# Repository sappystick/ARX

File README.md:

# Arx: PHI-FOLD 233 detector head (design repo)
Everything from the engineering sessions in one place: parametric CAD generators, PCB tooling, simulations, verified results, documents, ready-made prompts and Claude Code / Cowork configuration.

## Quick start (Claude Code or a plain terminal)
```
pip install -r requirements.txt
make setup
make verify-quick        # about 3 minutes: v5 cylinder + base plate + parts + 47 checks + transmit-stage and field simulation
python3 tests/regress.py
```
`make verify-full` (incl. `make audit-system`: wiring audit, stress table, stack-up, voxel interference) adds the receiver simulations, hood, yoke and the display-board routing and Gerbers. Then paste prompts/P00_BOOTSTRAP_CLAUDE_CODE.md into Claude Code.

## What is where
- docs/: DESIGN_STATE (current design), CORRECTIONS (what was wrong), ASSUMPTIONS, OPEN_ITEMS, PROCESS, CONVENTIONS, HISTORY, figures, reference photos.
- prompts/: P00-P10 for Claude Code (the next engineering tasks), prompts/cowork/C00-C06 for Cowork.
- .claude/: slash commands (/status /verify /newpart /route /release), skills, subagents, settings. CLAUDE.md at the root is the project memory.
- src/: generators and simulations (current) + archive/. data/: seeds, legacy boards, results, Gerbers. stl/: curated final STLs with hashes (formers are generated: `make formers-print`).
- scripts/push_to_github.sh: publish to GitHub yourself (plain git; STLs are ordinary binary files, all under GitHub's 100 MB limit).

## Honest scope
Nothing here has been printed, wound, assembled or measured. Performance numbers are modeled from stated assumptions. SB1R-QA/QB, LB1 and CB1D now have KiCad files and Gerbers that pass the repo's own checks and independent DRC; none has been opened in KiCad or a CAM viewer. The rigid-flex spine, CAM/KiCad verification and the DSP are open; the upper assembly (S-stem, trigger, battery dock, twin-cavity shaft) is generated and checked on its meshes but not printed (docs/OPEN_ITEMS.md, docs/design/UPPER_ASSEMBLY_v1.md).

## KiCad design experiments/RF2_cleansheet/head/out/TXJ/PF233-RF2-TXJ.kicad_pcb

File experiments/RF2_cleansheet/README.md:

# RF2 clean-sheet side experiment: transmit formation in a 1-inch head (MODELED)

Question (owner, 2026-10-29): inside the existing diameter and a 1-inch (25.4 mm) height, which layered / stacked / dense transmit-coil formation gives
the most depth together with the best signature data, with the dual-quadrupole receiver (RX-Q) and a central rigid-flex compute bay?
Nothing here touches the baseline. All numbers are MODELED: noise-limited, gold spheres, no ground, no bench data.

`rf2_coil_search.py` (about 20 s) -> `results/rf2_coil_search.json`; `rf2_figure.py` -> `results/rf2_coil_search.png`.

## Method
- Same physics as `src/sim/sim_head1.py`, re-parametrised: RX-Q geometry and noise, sphere step-off response, gate schedule, SNR 3, lateral search grid,
  the turn-off circuit and the first clean gate from the nulled turn-off tail (floor 6 us).
- **Fair comparison:** every candidate gets the baseline's energy per pulse at boost (1/2 x 54 uH x 20 A^2 = 10.8 mJ) and 20 A per switch. With the energy
  fixed, depth depends on the winding geometry through B / sqrt(L) only; the series / parallel split just trades current for inductance, and more switches
  (more total current at the same energy) make the turn-off faster.
- Coil: circular turns (exact elliptic-integral fields and inductances), litz 1.2 mm OD on a dense 1.6 mm grid, window z 3.2-21.9 mm (RX-Q boards below,
  lid + ferrite sheet + clearance above; the display sits in the centre bay), r up to 113.4 mm.
- **Validation:** the built coil through this chain: L 51.5 uH (model 54), 25.0 uT/A at 100 mm (24.56), moment 7.97 A m2 at 20 A (7.96), depth
  0.1 / 1 / 20 g = 90 / 134 / 188 mm (sim_head1: 91 / 136 / 189).

## Results (1 g / 0.1 g gold sphere, RX-Q)
| Formation | 1 g | 0.1 g | Notes |
|---|---|---|---|
| Built coil (25.6 mm tall, does not fit 1 in) | 134 | 90 | first gate 7.1 us |
| 1 in, dense window r 62-113 (spread) ... r 100-113 (rim), 1 switch | 136 | 91-92 | geometry changes depth by <= 1 mm at fixed energy |
| 1 in, rim r 100-113, 2 or 4 switches | 137 | 94 | turn-off 3.8 -> 1.9 us; first gate reaches the 6 us receiver floor |
| + ideal ferrite plane above (UPPER BOUND) | 143 | 98 | the real hood v3 model gave about half of an ideal plane's gain |
| Quadrant set, X mode (horizontal field, shape probe) | 131 | 93 | nearly as deep as the vertical mode with RX-Q |
| Built coil with the figure-8 receiver (sim_head1) | 152 | 99 | the receiver, not the transmit formation, is the largest depth lever |

First-gate sensitivity (4-switch rim coil): 6 / 4 / 3 / 2 us -> 0.05 g 79 / 85 / 88 / 91 mm, 0.1 g 94 / 98 / 100 / 102 mm, 1 g 137 / 139 / 139 / 140 mm.

## Reading
1. **A 1-inch head costs no depth.** At the same pulse energy the dense 1-inch windings match or beat the 25.6 mm stacked coil (136-137 vs 134 mm).
2. **No transmit formation is a big depth lever in this footprint.** Spreading or concentrating the turns, stacking or not: <= 2 mm. Depth moves with
   pulse energy (signal ~ sqrt(E): 2 x energy -> about +7 %), the receiver (figure-8 152 vs RX-Q 136 mm: RX-Q trades about 11 % depth for bearing and
   pinpoint), noise and averaging.
3. **Best formation for depth + signature:** a dense rim winding (r about 100-113 mm, full window height) split into interleaved full-ring branches on
   2-4 switches: fastest turn-off at the same energy (better small / fast targets once the receiver recovers sooner), same depth, frees the centre bay.
4. **Quadrant windings (Z + X / Y modes) give a strong shape channel (X mode 131 mm at 1 g) but a 1 % current mismatch between quadrants puts about
   0.49 V into RX-Q at turn-off** (the built coil's aligned leak is 0.01 mV). The vertical mode must stay on symmetric full-ring branches; X / Y needs
   its own matched pair winding and a receiver that recovers from that leak. Not yet modeled: the pairs' turn-off, X-mode energy, recovery.
5. **Small targets:** the remaining limit is the receiver recovery floor, not the coil: 6 -> 2 us adds about 15 % depth on 0.05 g.

## Not modeled
Ground (mineralisation: the early gates that help small gold also see more ground), coil self-capacitance, litz AC resistance, eddy currents in the head
and the compute bay, the real (finite) ferrite sheet, thermal. Next if pursued: figure-8 / DD / concentric receive options in the same chain with the
rim coil, a matched X / Y pair winding with its turn-off and leak, a finite ferrite sheet, and ground.

## Step 2: receiver architecture, light coil, mass, and an SDC 2300-class comparison (`rf2_receiver_combo.py`, `results/rf2_receiver_combo.{json,png}`)
Owner: targets of 1 g and up only. Same physics and equal energy per pulse (10.8 mJ); every receive channel read with the same preamp noise (1.7 nV/rtHz).

| Architecture (1-inch head, rim transmit coil) | 1 g | 5 g | 20 g | Uniform-ground coupling (rel. CN) |
|---|---|---|---|---|
| QUAD only (built receiver) | 137 | 165 | 190 | 0 by symmetry |
| Figure-8 only (check: sim_head1 at the same noise gives 179 mm at 1 g) | 181 | 223 | 262 | 0 by symmetry |
| Concentric nulled (12 turns r 80-95, 26 bucking turns r 65) | 231 | 284 | 337 | 1.0 |
| **Proposed: rim mono (26 turns, 321 uH, 8.2 A) + QUAD board, mono channel, 15 us gate** | **345** | **439** | **>= 500** | 1.44 |
| same, QUAD channel (bearing, pinpoint, depth ratio) | 131 | 162 | 189 | 0 by symmetry |
| SDC 2300-class 8 in mono at EQUAL electronics, 10 us gate (internals ASSUMED) | 330 | 413 | 494 | 1.40 |

- **Light transmit winding:** 24 turns (16.9 m of litz) give the same depth as the 99-turn dense window (66.6 m): at fixed energy only B / sqrt(L) counts.
- **Depth readout:** the QUAD / mono peak-signal ratio falls monotonically with depth (0.118 / 0.026 / 0.0094 / 0.0043 / 0.0019 at 50 / 100 / 150 / 200 / 300 mm),
  independent of target size for a sphere: depth from the ratio, then size from the amplitude at that depth, type from the decay time constant.
- **Head mass estimate: about 0.53 kg** (component estimates, not weighed; baseline head estimate 2.22 kg). The SDC 2300 is 2.3-2.4 kg as a whole
  detector without batteries; its coil mass is not published, so no head-to-head mass comparison is made.
- **SDC 2300 published facts used:** 8 in round mono, hardwired; Multi Period Fast PI; 2.3-2.4 kg without batteries; 4 x C cells, about 7 h; no
  discrimination, depth readout or pinpoint mode; LED indicator + audio; waterproof 3 m. Not published: turns, inductance, current, timing, noise, depth.
  The SDC row is therefore an 8 in mono with OUR electronics, not the real detector.
- **Reading:** the mono channel is the deepest receive option for >= 1 g (the full transmit coil is the receiver: the largest area); the proposed
  head's mono is about 4-5 % deeper than an 8 in mono at equal electronics, from the larger diameter only. What the proposed head adds is the QUAD
  channel (bearing, peak-null-peak pinpoint, a ground-symmetric second channel) and the ratio depth readout.
- **The bucking-turn cap:** an unconstrained concentric search chose 1239 turns at r 12 mm (cannot be laid out; capacitance and resistance noise not
  modeled); the search caps the bucking winding at 30 board-trace turns (0.3 mm pitch, 4 layers, a 6 mm band holds about 80).
- **Not modeled, and decisive in the field:** real ground. The mono and CN channels see a uniform viscous ground strongly and need ground balance
  (as the SDC has); the QUAD and figure-8 cancel uniform ground only while the head stays level and at constant height. Hot rocks, layering and
  sweep tilt are not modeled. Also not modeled: the mono's damping-resistor noise and preamp overload recovery (the 1.7 nV/rtHz is generous to both
  monos), self-capacitance, eddy currents in the compute bay.

## Step 3: mineralised ground and how to cancel it (`rf2_ground.py`, `results/rf2_ground.{json,png}`)
Ground model (Born approximation, uniform magnetically viscous half-space, ASSUMED parameters swept): emf = I chi_v / mu0 x G(h, tilt) x [t^-a - (t+T)^-a];
G = integral of Bt . Br over the ground. Varies while sweeping: height 15-45 mm, tilt about 3 deg, exponent a = 1 +- 0.03, patchy amplitude x lognormal(0, 0.3).
chi_v 2e-6 / 2e-5 / 2e-4 (mild / moderate / severe) is an ASSUMED order of magnitude, not a measured soil. Optimal linear detectors (SINR = s' R^-1 s).

| 1 g depth (mm) | none | mild | moderate | severe |
|---|---|---|---|---|
| D1 mono, no ground balance | 362 | 0 | 0 | 0 |
| D2 mono, time-domain balance | 366 | 244 | 221 | 204 |
| **D3 mono, multi-period (PWM flat-top) balance** | 367 | **249** | **228** | **221** |
| D4 quadrupole pair only, no balance | 137 | 128 | 88 | 0 |
| D5 / D6 mono + QA + QB space-time (with / without multi-period) | = D2 / D3 | | | |
| D7 + dual transmit (inner coil, alternate pulses) | 350 | 239 | 220 | 212 |
| SDC 2300-class 8 in mono, multi-period (equal electronics) | 342 | 235 | 216 | 209 |

- The quadrupole sees uniform ground only through tilt, at second order (level ground: 1e-29 vs the mono's 4e-11; 3 deg tilt about 1e-3 of the mono).
- In uniform ground the time signature does the work: multi-period (two PWM on-times) is the best method; the quadrupole array and dual transmit add nothing
  (dual transmit splits the pulses and loses a little).
- What costs depth is the spread of the ground's decay exponent: tracking it (severe ground, 1 g) 0.03 -> 0.01 -> 0.003 -> 0: 221 -> 227 -> 249 -> 274 mm.
  Even a perfectly known exponent leaves about 25 % loss against no ground: the unknown 1/t amplitude overlaps the target's decay.

## Step 4: a firmware-style ground-tracking detector on simulated sweeps (`rf2_ground_dsp.py`, `results/rf2_ground_dsp.json`)
Frames of 36 numbers (mono at both PWM periods, QA / QB with both periods averaged: every pulse is received by every coil); ground learned as a low-rank
subspace per receiver (eigen-directions above the electronic noise, EWMA, an 80-frame "ground pump" at switch-on, a guard window so a target's flanks are
not learned, an anti-lock rule); GLRT over a bank of 12 decay constants, silent below the chi-square threshold (false-alarm rate 1e-5 per frame).
- **0 false-alarm frames** on target-free sweeps over severe and moderate ground.
- 1 g detected at 100, 150, 200 mm (severe and moderate); decay constant 27.3 us against 27.9 us true -> "small gold". 5 g at 250-280 mm and 20 g at
  300 mm were NOT detected in one pass (peak statistic 20-24 vs threshold 25.9): the adaptive detector with a strict false-alarm rate reaches less than
  the oracle study above.
- Readouts, honestly: the quadrupole's single-pass range for 1 g is about 80-100 mm (noise-only check: SNR 29 / 4 / 0.5 at 60 / 100 / 150 mm), so bearing
  and ratio depth only work close in; the mono response width resolves depth only beyond about 160 mm (the 230 mm coil sets a floor); between, depth
  is "<= 160 mm" and size an upper bound. Next: a trigger-held pinpoint (boost + averaging) for bearing / depth / size, and the 100-160 mm gap.
- Mistakes found and fixed on the way: rank 3 ground subspace (the ground needs about 7 directions: 79 of 81 frames falsely triggered); a quadrupole
  "signal" that was the best of 81 noise frames (gate raised to SNR 5); a tracker that learned the target's flanks (guard window); quadrupole fed only
  half the pulses.

## Step 5: is every coil fully off when the receivers listen? (`rf2_timing.py`, `results/rf2_timing.json`)
Two coupled coils with node capacitance, damping, clamp diode / capacitor and the switch's body diode; nonlinear part by ODE, linear tail exact (matrix
exponential, resolved to 100 nV); preamp recovery 2 us and coil capacitance 500 pF ASSUMED.

| Case (first clean gate, us) | mono | QUAD | current induced in idle coil B |
|---|---|---|---|
| rim coil alone, critical damping | **16.3** | 9.2 | - |
| rim coil alone, baseline damping ratio (underdamped) | 24.8 | 13.5 | - |
| + idle B wound the same sense | 21.7 | 11.6 | 0.34 A (through its damping only) |
| + idle B wound the opposite sense | **36.7** | 24.0 | **1.5 A** (its switch's body diode conducts) |
| + idle B, clamp not yet charged (first pulses) | 27.2 | 17.1 | 1.6 A |

- The assumed 15 us mono gate holds for a critically damped mono (16.3 us): 1 g depth 363 vs 367 mm, severe ground 221 either way. Use critical damping.
- Dual transmit needs: both coils wound the same sense, clamps pre-charged before the first pulse, and about 5 us more delay from the idle coil's damping.
- Nothing is left at the 2.5 ms period (residual about 0).

## Step 6: trigger-held pinpoint (`rf2_pinpoint.py`, `results/rf2_pinpoint.json`)
After a detection: hold the trigger and make one slow pass back over the spot (+-250 mm), BOOST 2.5 x energy per pulse (about 13 A, inside the 20 A switch
rating, a few seconds) and k = 4 or 16 x more pulses per 10 mm frame. Same tracker and detector as step 4.
- **Bearing works close in:** 1 g at 100 mm: quadrupole SNR 5-9 (scan pass 2.6-2.9), bearing axis within about 1-11 deg of the truth (e.g. 166.9 vs 167.5,
  168.1 vs 168.7, 139.8 vs 128.7); depth from the quadrupole / mono ratio 80-88 mm (biased low, true 100); size 0.6-0.8 g (true 1 g).
- **It does not close the 100-160 mm gap:** from 130 mm the quadrupole stays at SNR 2-4 even 16 x slower with boost, while the mono statistic grows
  10-30 x. The quadrupole there is limited by ground reaching it through head tilt and by its own steep fall-off, not by noise; averaging cannot fix it.
- **Lift test (second pass 50 mm higher; ratio of the two mono peaks, size-independent): NOT working yet.** With the scan height wobble (sd 8 mm) the
  ratio is dominated by the unknown height (about 25 % per 8 mm at 150 mm range); with the height known exactly the errors are still 20-50 % (1 g at
  130 mm -> 108, 5 g at 200 mm -> 276). Fixed on the way: both passes must be fitted at the same decay constant. Unresolved error sources (tilt per frame,
  10 mm sampling, the tracker re-learning between passes) are open. A deep depth readout needs a known height (ground-referenced height from the
  ground signal itself, a height sensor, or a rest-on-the-ground pinpoint with a fixed lift spacer) and this error budget resolved.

## Step 7: golden-angle petals in a thin ring around the rim (owner idea; `rf2_petal_ring.py`, `results/rf2_petal_ring.json`)
Same chain and equal energy per pulse; the petal set is transmitter and receiver (mono style); first gate 16.3 us; noise-limited, no ground.
| Formation (1 / 5 / 20 g, mm) | 1 g | 5 g | 20 g | net moment, A m2 |
|---|---|---|---|---|
| Reference: rim mono, 26 turns | 342 | 437 | >= 500 | 8.23 vertical |
| Best petal ring: 8 flat petals, radius 40 mm, 1 layer | 242 | 312 | 379 | 4.90 vertical |
| 6 flat petals r 25 mm / 13 flat petals r 15 mm | 132 / 84 | 185 / 121 | 237 / 165 | 1.92 / 1.38 |
| Best standing (radial) petals: 8 x r 40 mm, 6 layers | 187 | 230 | 267 | about 0.1 horizontal |
| Tangential petals | 0-118 | 0-136 | 0-151 | about 0.1 horizontal |
Reading: depth follows the magnetic moment (turns x current x enclosed area) the coil can make with the pulse energy. One loop around the full rim
encloses the most area; splitting the same wire into small petals encloses far less (moment 4.9 vs 8.2 A m2 at best), and standing petals point their
moments in different directions around the ring, which nearly cancel (net about 0.1 A m2): their field falls off faster and the depth drops. The golden
angle changes the near-field pattern, not the far field that reaches depth. Layering petals vertically does not recover it.

## Step 8: separate jobs: rim coil transmits, a disc coil in the centre receives (owner idea; `rf2_disk_rx.py`, `results/rf2_disk_rx.json`)
Unnulled receive coil on the base board (2 oz traces, 150 pF and 2 us preamp recovery ASSUMED, critically damped); first gates from the coupled turn-off;
noise includes the coil resistance and its damping resistor; the rim coil's own mono channel is kept as a second channel (SNR combined in quadrature).
| Receive pattern, turns | first gate, us | 1 g: disc / mono / both | 5 g: disc / mono / both | flyback on the receive coil |
|---|---|---|---|---|
| inner r 15-60, 48 | 16.7 | 272 / 340 / 343 | 346 / 436 / 439 | 67 V |
| disc r 15-100, 48 | 20.2 | 310 / 336 / 348 | 398 / 434 / 447 | 199 V |
| sunflower (equal area per turn) r 15-100, 48 | 21.8 | 323 / 334 / 351 | 416 / 433 / 453 | 265 V |
| **outer ring r 85-100, 48** | 26.7 | **344 / 327 / 359** | **448 / 429 / 467** | **484 V** |
- The best separate receiver matches the rim coil as its own receiver (344 vs 327-341 mm at 1 g); both channels together add about 5 % (359 mm).
- Why not more: the rim coil as a receiver already encloses the largest area possible in this footprint; a disc inside it encloses less, and more
  turns raise its signal but slow its recovery (gate 16.7 -> 26.7 us) and its coupling to the transmitter (k up to 0.51).
- Ground pickup is the same order as the mono (0.8-0.97 of it): the disc receiver needs ground balance too.
- High voltage: unnulled, the receive coil sees up to 484 V at turn-off, so its board falls under rule 6 (>= 1.0 mm clearance, 630 V input
  protection) unless a bucking winding nulls it (step 2: the nulled concentric receiver reached 231 mm).

## Step 9: external interference and cancelling it (`rf2_emi.py`, `results/rf2_emi.json`)
Interference amplitudes and spectra ASSUMED (swept), uniform over the head; 1 g depth, mono / quadrupole (0.1 % lobe imbalance ASSUMED), mm.
| Source | matched, fixed rate | matched, jittered | learned, fixed | learned, jittered | learned + jitter + 3-axis REF on the shaft |
|---|---|---|---|---|---|
| none | 360 / 138 | 360 / 138 | 364 / 139 | 364 / 139 | 360 / 139 |
| power line, rural 0.05 uT | 164 | 193 | 273 | 288 | **349** |
| power line, under a line 1 uT | 51 | 74 | 222 | 230 | **295** |
| VLF 1 nT at exactly 20.000 kHz (in step with 400 Hz) | 130 | 225 | 354 | 354 | 360 |
| VLF 10 nT at 19.8 kHz | 360 | 130 | 364 | 353 | 359 |
| electric fence 50 nT at 20 m (1 pulse/s) | 173 | 176 | 327 | 205 | **360** (fence pulses blanked) |
The quadrupole stays at 138-139 mm in every case: it rejects uniform interference by symmetry (net area 0; the imbalance leaks about 1e-5 of the mono).
- **Learning the interference** (listen-only frames, whitening) is the largest single step: steady interference makes a fixed pattern across the gates
  that the detector can cancel. **Jitter is not always better**: it helps a simple matched detector against an in-step tone (130 -> 225), but it
  turns a learnable pattern into noise for the learning detector, and for a tone near (not at) a pulse-rate multiple the fixed rate already cancels it
  (19.8 kHz: fixed 360, jittered 130). The firmware should choose the rate per site (like an automatic frequency offset), not jitter blindly.
- **The 3-axis reference coil** (0.6 m up the shaft, adaptive weights) recovers most of the power-line loss (230 -> 295 under a line; 288 -> 349 rural)
  and, with blanking, all of the fence loss; its own noise costs about 1 % depth. Residual: the field difference between the shaft and the head (3 %
  for a line source at 20 m). Fence results vary from run to run (few hits per run).
- **Split-ring (MWO-style) shield**: a split 3 mm trace's own eddy decay is about 0.8 us (1 mm trace 0.26 us), down by e^-21 at the 16.3 us first gate;
  the same trace closed into a ring decays with 6 us, inside the receive window. Split rings are eddy-safe as an electrostatic shield; closed rings are not.
  (An earlier statement in the session that the split trace decays in about a nanosecond was wrong by a factor of 1000; corrected here.)

## Step 10: head v1 layout, seats, shield board, wiring, power and timing (`head/`, `HANDOFF_RF2.md`)
The design implementation set: `head/rf2_head.py` (spec + every printed part, seat and envelope), `head/rf2_shield_pcb.py` (SH1: KiCad DRC 0 / 0, Gerbers +
drill, loop-free), `head/rf2_head_check.py` (measured checks, all pass; mass about 702 g), `head/rf2_wiring.py` (C01-C12, ADC map, power, timing; slot
probes), figures `head/out/rf2_head_layout.png` and `head/out/rf2_wiring.png`. Every part, function and open step: `HANDOFF_RF2.md`.

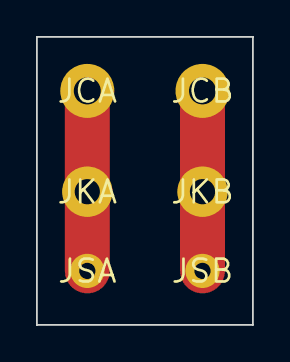
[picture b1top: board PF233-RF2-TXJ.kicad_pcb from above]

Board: 2 copper layers, 12.0 x 16.0 mm, 6 parts (0 on the bottom side), 2 nets.

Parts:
JCA: coil A; WIRE_LITZ
JCB: coil B; WIRE_LITZ
JKA: cable A; WIRE_AWG18
JKB: cable B; WIRE_AWG18
JSA: sense A; WIRE_SENSE
JSB: sense B; WIRE_SENSE

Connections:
TX_A: JCA.1, JKA.1, JSA.1
TX_B: JCB.1, JKB.1, JSB.1

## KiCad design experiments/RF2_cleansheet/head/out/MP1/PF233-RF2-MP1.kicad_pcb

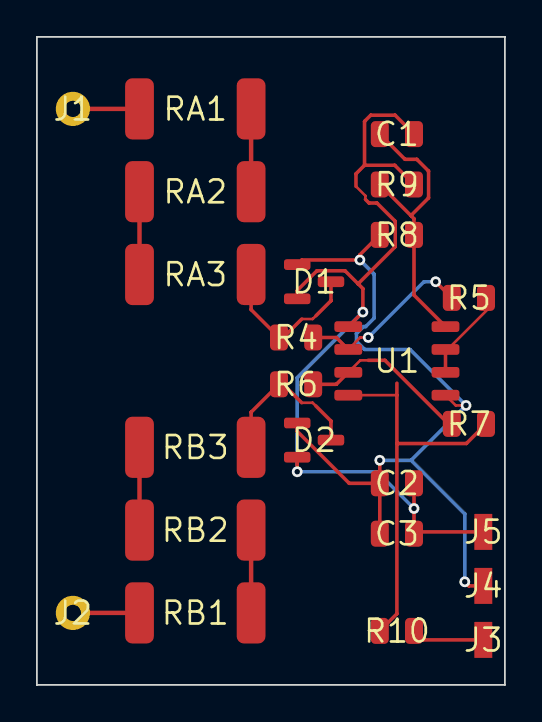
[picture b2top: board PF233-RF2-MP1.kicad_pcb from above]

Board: 2 copper layers, 26.0 x 36.0 mm, 24 parts (0 on the bottom side), 16 nets.

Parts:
C1, C3: 100n; C0805
C2: 10u; C0805
D1, D2: BAV199
J1: COIL_A; WIRE_SENSE
J2: COIL_B; WIRE_SENSE
J3: MONO_OUT; FLEX_PAD
J4: +5VA; FLEX_PAD
J5: AGND; FLEX_PAD
R4, R6: 1k; R0805
R5, R7: 24k; R0805
R8, R9: 10k; R0805
R10: 100R; R0805
RA1, RA2, RA3: 470R CRCW2512; R2512
RB1, RB2, RB3: 470R CRCW2512; R2512
U1: OPA2211AIDR; OPA2211

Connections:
+5VA: C2.1, C3.1, D1.2, D2.2, J4.1, R8.1, U1.8
AGND: C1.2, C2.2, C3.2, D1.1, D2.1, J5.1, R9.2, U1.4
COIL_A: J1.1, RA1.1
COIL_B: J2.1, RB1.1
HA1: RA1.2, RA2.1
HA2: RA2.2, RA3.1
HB1: RB1.2, RB2.1
HB2: RB2.2, RB3.1
INN: D2.3, R6.1, RB3.2
INP: D1.3, R4.1, RA3.2
MINUS_A: R6.2, R7.1, U1.2
MONO_OUT: J3.1, R10.2
OUT_A: R7.2, R10.1, U1.1
PLUS_A: R4.2, R5.1, U1.3
VBIAS: R5.2, U1.6, U1.7
VDIV: C1.1, R8.2, R9.1, U1.5
